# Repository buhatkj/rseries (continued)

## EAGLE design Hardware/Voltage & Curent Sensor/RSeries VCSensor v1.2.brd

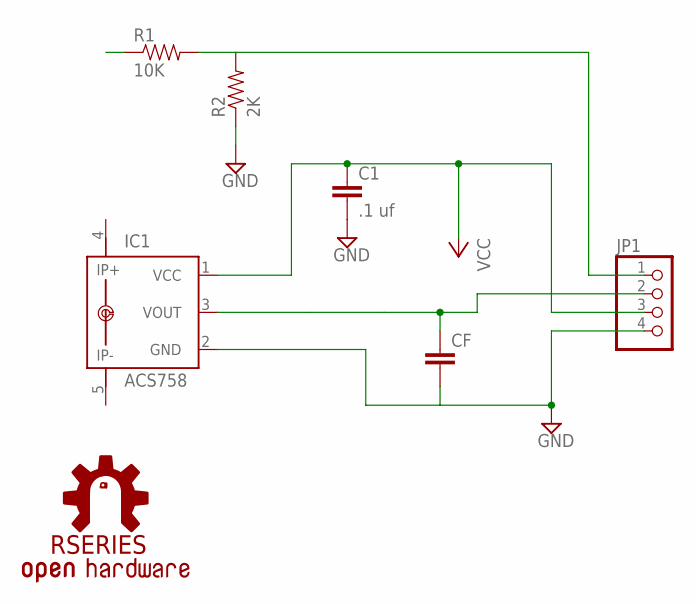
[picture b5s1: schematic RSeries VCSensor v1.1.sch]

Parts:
C1: .1 uf; CAP-PTH-SMALL
CF: CAPPTH1; CAP-PTH-5MM
IC1: ACS758; CB-PFF
JP1: PINHD-1X4; 1X04
R1: 10K; AXIAL-0.4
R2: 2K; AXIAL-0.4
U$1: RSERIES-OSHW-LOGO; RSERIES-OSHW-LOGO-LARGE

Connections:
GND: C1.2, CF.2, IC1.2 (GND), JP1.4, R2.P$1 (1)
unnamed: CF.1, IC1.3 (VOUT), JP1.2
unnamed: JP1.1, R1.P$2 (2), R2.P$2 (2)
VCC: C1.1, IC1.1 (VCC), JP1.3

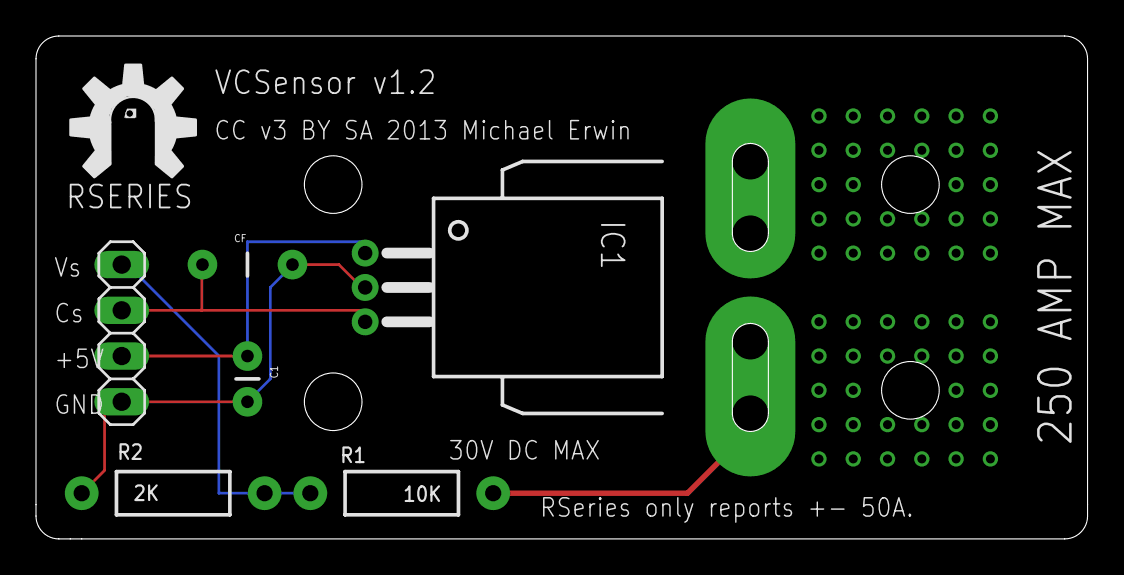
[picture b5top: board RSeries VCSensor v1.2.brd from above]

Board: 2 copper layers, 58.4 x 27.9 mm, 8 parts (1 on the bottom side), 4 nets.

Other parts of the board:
U$3: ROYAL-ENGINEERS-OF-NABOO-SMALL

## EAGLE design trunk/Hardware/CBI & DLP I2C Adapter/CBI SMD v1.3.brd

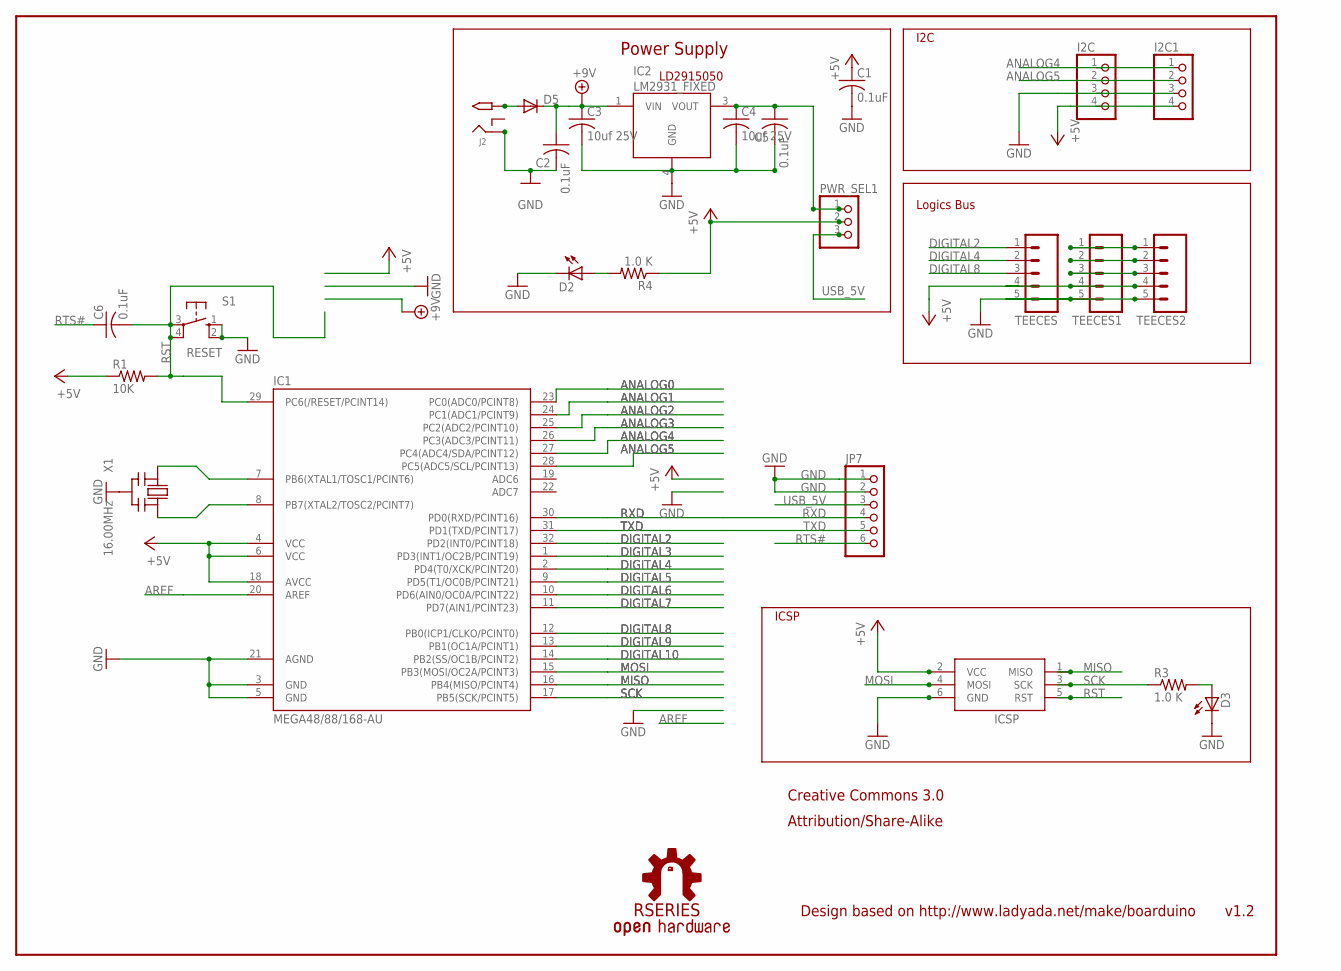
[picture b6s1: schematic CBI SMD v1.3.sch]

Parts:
C1, C2, C5, C6: 0.1uF; C1206K
C3, C4: 10uf 25V; C1206K
D2: LEDCHIPLED_1206; CHIPLED_1206
D3: Green; CHIPLED_1206
D5: DIODE-SMB; SMB
I2C, I2C1: PINHD-1X4CB; 1X04-CB
IC1: MEGA48/88/168-AU; TQFP32-08
IC2: LM2931_FIXED; DPAK
ICSP: AVRISP-6; AVRISP
J2: 2.1MMJACK; PJ-102A
JP7: PINHD-1X6CLEAN; 1X06-CLEAN
PWR_SEL1: PINHD-1X3; 1X03
R1: 10K; R1206
R3, R4: 1.0 K; M1206
S1: RESET; B3F-10XX
TEECES, TEECES1, TEECES2: M05PTH; 1X05
U$2: RSERIES-OSHW-LOGOMEDIUM; RSERIES-OSHW-LOGO-MEDIUM
X1: 16.00MHz; CERM_OSC

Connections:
+5V: C1.1, I2C.4, I2C1.4, IC1.4 (VCC), IC1.6 (VCC), IC1.18 (AVCC), ICSP.2 (VCC), PWR_SEL1.2, R1.1, R4.1, TEECES.4, TEECES1.4, TEECES2.4
+9V: C2.1, C3.1, D5.C, IC2.1 (VIN)
ANALOG0: IC1.23 (PC0(ADC0/PCINT8))
ANALOG1: IC1.24 (PC1(ADC1/PCINT9))
ANALOG2: IC1.25 (PC2(ADC2/PCINT10))
ANALOG3: IC1.26 (PC3(ADC3/PCINT11))
ANALOG4: I2C.1, I2C1.1, IC1.27 (PC4(ADC4/SDA/PCINT12))
ANALOG5: I2C.2, I2C1.2, IC1.28 (PC5(ADC5/SCL/PCINT13))
AREF: IC1.20 (AREF)
DIGITAL2: IC1.32 (PD2(INT0/PCINT18)), TEECES.1
DIGITAL3: IC1.1 (PD3(INT1/OC2B/PCINT19))
DIGITAL4: IC1.2 (PD4(T0/XCK/PCINT20)), TEECES.2
DIGITAL5: IC1.9 (PD5(T1/OC0B/PCINT21))
DIGITAL6: IC1.10 (PD6(AIN0/OC0A/PCINT22))
DIGITAL7: IC1.11 (PD7(AIN1/PCINT23))
DIGITAL8: IC1.12 (PB0(ICP1/CLKO/PCINT0)), TEECES.3
DIGITAL9: IC1.13 (PB1(OC1A/PCINT1))
DIGITAL10: IC1.14 (PB2(SS/OC1B/PCINT2))
GND: C1.2, C2.2, D2.C, D3.C, I2C.3, I2C1.3, IC1.3 (GND), IC1.5 (GND), IC1.21 (AGND), IC2.4 (GND), ICSP.6 (GND), J2.RING, JP7.1, JP7.2, S1.1 (S), S1.2 (S1), TEECES.5, TEECES1.5, TEECES2.5, X1.P$2 (GND)
MISO: IC1.16 (PB4(MISO/PCINT4)), ICSP.1 (MISO)
MOSI: IC1.15 (PB3(MOSI/OC2A/PCINT3)), ICSP.4 (MOSI)
unnamed: IC1.7 (PB6(XTAL1/TOSC1/PCINT6)), X1.P$1 (IN)
unnamed: IC1.8 (PB7(XTAL2/TOSC2/PCINT7)), X1.P$3 (OUT)
unnamed: TEECES1.3, TEECES2.3
unnamed: D3.A, R3.2
unnamed: D2.A, R4.2
unnamed: D5.A, J2.TIP
unnamed: TEECES1.2, TEECES2.2
unnamed: C3.2, C4.2, C5.2
unnamed: C4.1, C5.1, IC2.3 (VOUT), PWR_SEL1.1
unnamed: TEECES1.1, TEECES2.1
RST: C6.2, IC1.29 (PC6(/RESET/PCINT14)), ICSP.5 (RST), R1.2, S1.3, S1.4 (P1)
RTS#: C6.1, JP7.6
RXD: IC1.30 (PD0(RXD/PCINT16)), JP7.4
SCK: IC1.17 (PB5(SCK/PCINT5)), ICSP.3 (SCK), R3.1
TXD: IC1.31 (PD1(TXD/PCINT17)), JP7.5
USB_5V: JP7.3, PWR_SEL1.3

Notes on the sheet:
v1.2
Design based on http://www.ladyada.net/make/boarduino
Creative Commons 3.0
Attribution/Share-Alike
Logics Bus
I2C
ICSP
Power Supply
LD2915050

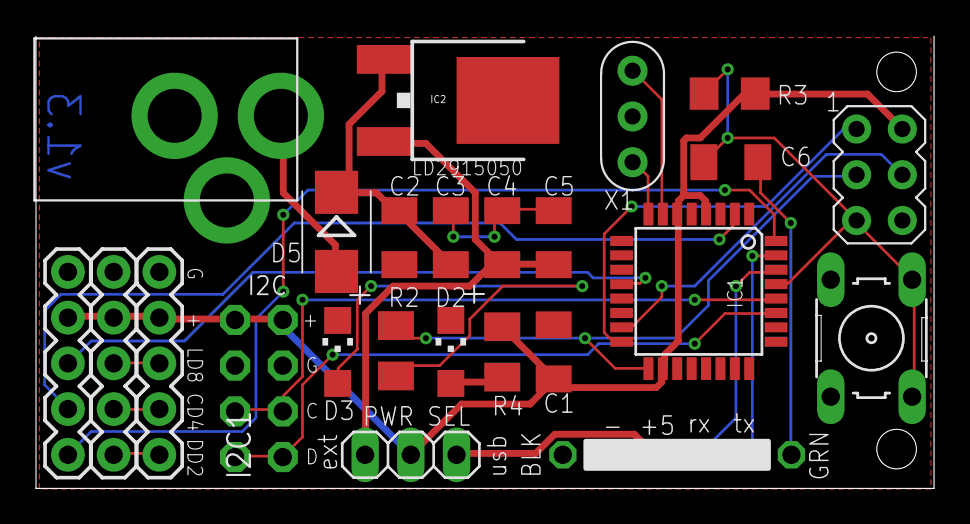
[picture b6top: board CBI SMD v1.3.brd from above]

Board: 2 copper layers, 49.9 x 25.1 mm, 26 parts (1 on the bottom side), 26 nets.
